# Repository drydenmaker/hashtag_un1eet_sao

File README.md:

# un1eet_sao
A #badgelife sao for the #un1eet. "ur #un1leet

Feel free to have it made, add some bling, whatever ur #un1eet.

## Support this crazy obsession:
  * on Tindie - https://www.tindie.com/products/13584/
  * stickers and such - https://rdbl.co/2uf2GzY 
  * this and other crazy designs - http://bit.ly/2KQ50Yd 
  * order from oshpark:
    * Non LED http://bit.ly/2us6NHX

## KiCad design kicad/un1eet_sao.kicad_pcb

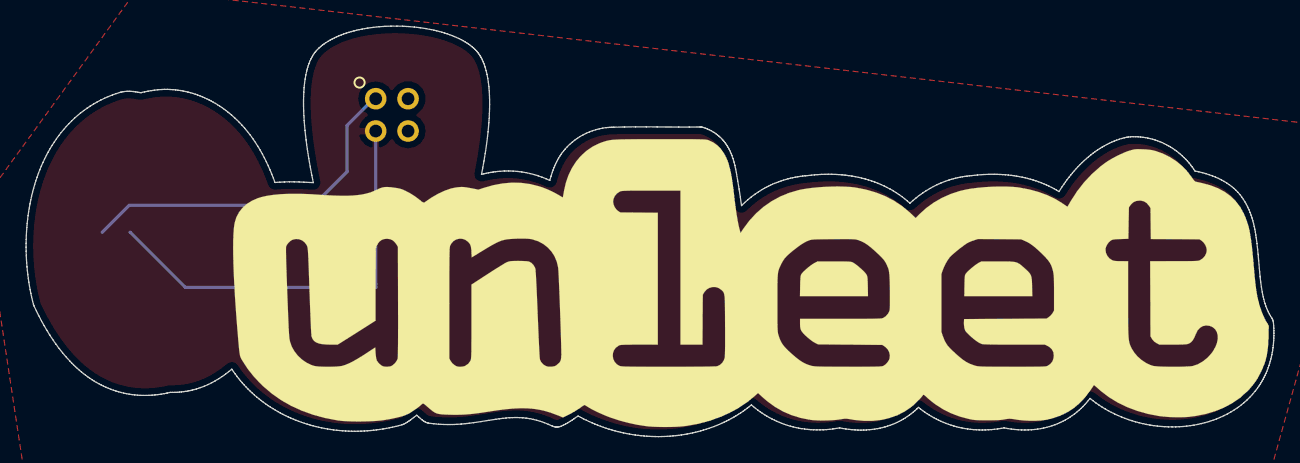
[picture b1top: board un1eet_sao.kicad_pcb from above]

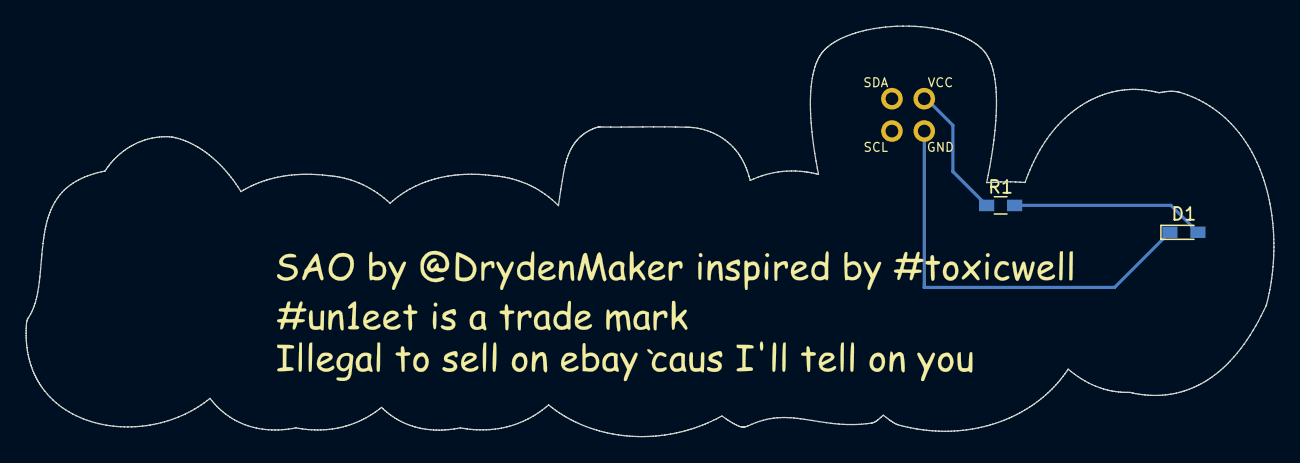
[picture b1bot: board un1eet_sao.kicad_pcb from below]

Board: 2 copper layers, 98.1 x 32.3 mm, 3 parts (2 on the bottom side), 3 nets.

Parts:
D1: LED; LED_0603_HandSoldering
J2: #badgelife; Badgelife-Shitty-2x2
R1: 330R; R_0603_HandSoldering

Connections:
GND: D1.1, J2.2
unnamed: D1.2, R1.2
unnamed: J2.1, R1.1

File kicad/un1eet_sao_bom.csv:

"Id";"Designator";"Package";"Quantity";"Designation";"Supplier and ref";
1;",";"F.Mask_g8167";2;"";;;
2;"";"B.Silk_g8163";1;"";;;
3;"J2";"Badgelife-Shitty-2x2";1;"#badgelife";;;
4;"";"F.Silk_g8169";1;"";;;
5;"R1";"R_0603_HandSoldering";1;"330R";;;
6;"D1";"LED_0603_HandSoldering";1;"LED";;;

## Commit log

2018-07-12 flipping back text
2018-07-12 adding sao
2018-07-12 adding sao connector
2018-07-12 removing old svg
2018-07-12 updating git ignore
2018-07-12 adding readme and licence
2018-07-12 adding renders
2018-07-12 adding images
2018-07-12 adding links to readme
2018-07-12 updating gerbers
2018-07-12 adding oshpark link
2018-07-12 Added a shitty led
2018-07-12 Created schematic with shitty led
2018-07-13 tweaking on the led
2018-07-13 adding led version link
2018-12-01 updating link
2019-06-16 cleaned up design
2019-06-22 adding mk2
2019-06-22 now more un1eet
